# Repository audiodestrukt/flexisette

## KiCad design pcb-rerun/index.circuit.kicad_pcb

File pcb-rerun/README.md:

# pcb-rerun — flexisette re-driven unattended (2026-10-04)

A side-by-side re-run of the PCB next to the shipped board in [`../pcb`](../pcb). Same circuit and
same floorplan, routed with nobody touching KiCad, using the current
[circuit-skills](https://github.com/punkfab/circuit-skills) tooling.

## Result

| | Shipped (`../pcb`, June) | Re-run (this folder) |
|---|---|---|
| Open connections | 10 | **0** |
| Shorts | 0 | 0 |
| DRC errors (JLCPCB rules) | 5 (3 hole clearance, 1 edge clearance, 1 drill) | **0** |
| SMD pads not reached on their own layer | 4 | **0** |
| Vias | 26 | 47 |
| Track length | 1263 mm | 1000 mm |
| Ground carried as track instead of pour | 350 mm | 44 mm |
| Route time | hours of iteration, then a ~10-net tail left for hand-finishing | 6 s |

Checks on the re-run board:

- KiCad DRC at every severity: 0 errors, 0 unconnected, 5 silkscreen warnings.
- `dfm_check` (hole spacing, via drill and annular ring) passes.
- `check_floating` passes for all 106 SMD pads.
- The netlist is identical to the shipped board's: 22 nets, the same pads on each.

It has not been through JLCPCB's online DFM or a human review. Do both before ordering.

## What changed

**The route starts from the placed KiCad board, not from tscircuit's DSN export.** `scripts/route2.sh`
exports the placement, strips tscircuit's own routing, adds the bottom ground pour, applies JLCPCB
rules, and then runs every router on the KiCad board itself and scores them
(`scripts/route_eval.py`). Freerouting goes through KiCad's own Specctra export and import. The pour
goes out as a plane and the tape window, reel holes and screw holes go out as keepouts, so the router
sees the real board. This also closes roadmap gap #1 ("round-trip placement doesn't reach the routing
DSN"): there is no second copy of the placement to drift.

**Three placement changes**, each named by the tooling and made in the design source:

| Part | Change | Why |
|---|---|---|
| `SW_A`, `SW_B` | up 0.5 mm | A button pad was 0.455 mm from the head-notch edge. |
| `C1` (ESP32 3V3 decoupling, bottom side) | 2 mm inboard, under the module | Directly under the pin it sat against the board edge, and one bottom track boxed its ground pad off from the pour. |
| `C_BAT` | moved to the charger's BAT pin, placed by pin (`Decap`) | It was on the far side of the charger, 5 mm of crowded routing from the pin it decouples. Freerouting left that connection open. |

**Four tooling fixes** this board forced, all now in circuit-skills:

- **Ref-less footprints.** KiCad silently refuses to export a board that has a footprint with an empty reference. tscircuit exports bare holes and vias that way, which is why Freerouting-on-the-KiCad-board had never worked on a tscircuit design.
- **Keepout margin.** Cutout keepouts are grown by the copper-to-edge clearance. Otherwise a track ran 0.14 mm from the tape window.
- **Pour connection.** The pour connects SMD pads solidly, with thermal reliefs on through-hole pads only.
- **Capacity autorouter outline.** `route_srj` now gives the router the real outline polygon and the cutouts. It used to see only the bounding box.

The capacity autorouter's candidate also connects everything with no shorts, but leaves 14 clearance
violations (`results/candidate-srj.kicad_pcb`). Freerouting's is the one kept.

## Reproduce

```bash
cd pcb-rerun
npm install                 # or: ln -s ../pcb/node_modules node_modules
bash scripts/route2.sh      # ~30 s: export -> gates -> prep -> route with every backend -> apply the best -> DRC
```

Needs bun/tsci, KiCad 9 (`kicad-cli` and the system python `pcbnew` module), and Freerouting 2.2.4
(`freert224`). No running KiCad is required.

## results/

| file | what |
|---|---|
| `compare.jpg` | shipped vs re-run, with open connections and DRC errors marked |
| `route-eval-summary.md` | the scored table for both routers and the diagnosis |
| `candidate-srj.kicad_pcb` | the capacity autorouter's candidate |
| `placement-heat.svg` | congestion map of the placement before routing |

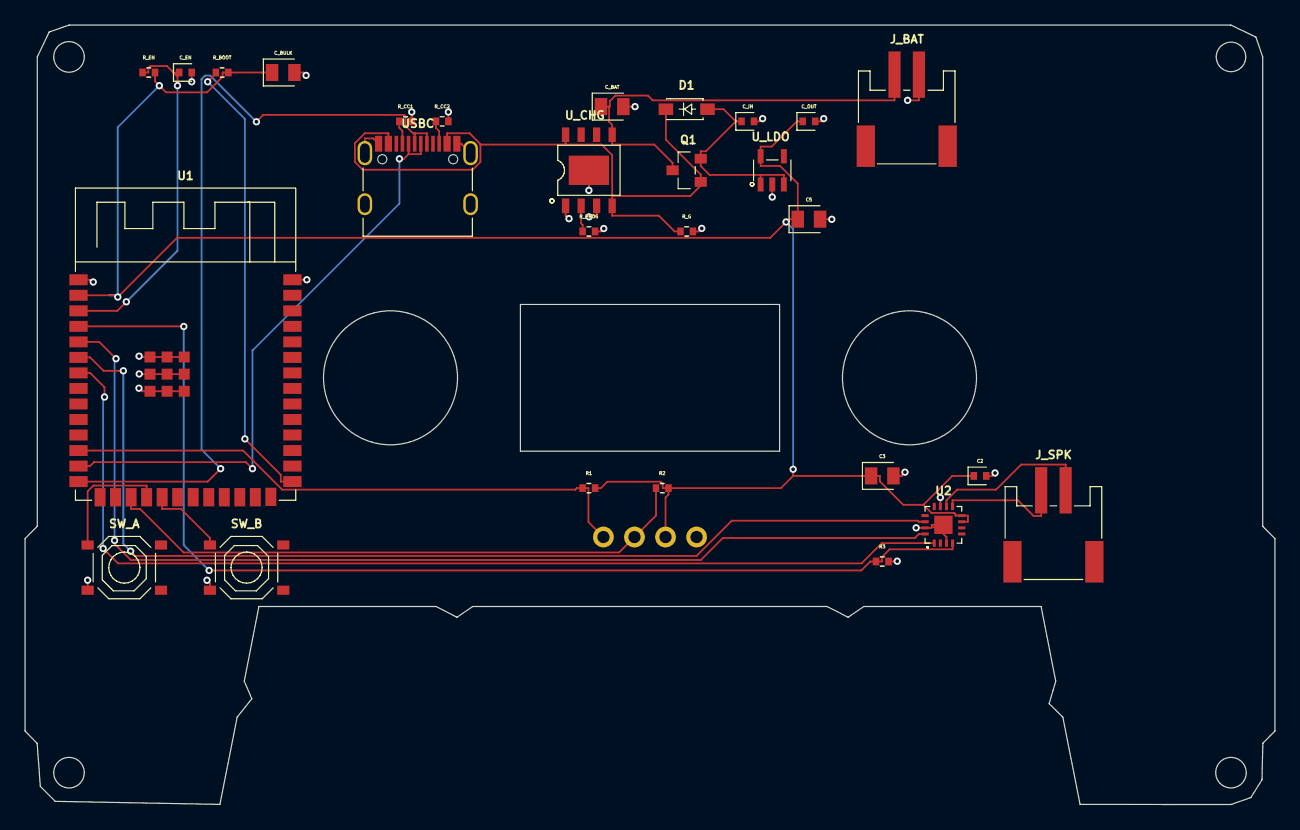
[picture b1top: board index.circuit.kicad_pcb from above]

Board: 2 copper layers, 102.2 x 63.8 mm, 30 parts (0 on the bottom side), 22 nets.

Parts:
C1, C2: 100nF; capacitor_0402
C3: 10uF; capacitor_0805
C5: 22uF; capacitor_0805
C_BAT: 10uF; capacitor_0805
C_BULK: 22uF; capacitor_0805
C_EN: 100nF; capacitor_0402
C_IN: 1uF; capacitor_0402
C_OUT: 1uF; capacitor_0402
D1: D; B5819W_SL
J_BAT: S2B_PH_SM4_TB_LF__SN_; S2B_PH_SM4_TB_LF_SN
J_SPK: S2B_PH_SM4_TB_LF__SN_; S2B_PH_SM4_TB_LF_SN
OLED: chip
Q1: AO3401A
R1, R2: 4.7kΩ; resistor_res0402
R3: 100kΩ; resistor_res0402
R_BOOT: 10kΩ; resistor_res0402
R_CC1, R_CC2: 5.1kΩ; resistor_res0402
R_EN: 10kΩ; resistor_res0402
R_G: 100kΩ; resistor_res0402
R_PROG: 2kΩ; resistor_res0402
SW_A: TS_1187A_B_A_B
SW_B: TS_1187A_B_A_B
U1: ESP32_S3_WROOM_1_N16R8
U2: MAX98357AETE_T
USBC: TYPE_C_31_M_12
U_CHG: TP4056_42_ESOP8
U_LDO: ME6211C33M5G_N

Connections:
BCK: U1.5, U2.16
DIN: U1.7, U2.1
GND: C1.2, C2.2, C3.2, C5.2, C_BAT.2, C_BULK.2, C_EN.2, C_IN.2, C_OUT.2, J_BAT.2, OLED.1, R3.2, R_CC1.2, R_CC2.2, R_G.2, R_PROG.2, SW_A.3, SW_B.3, U1.1, U1.40, U1.41, U1.42, U1.43, U1.44, U1.45, U1.46, U1.47, U1.48, U1.49, U2.3, U2.11, U2.15, U2.17, USBC.1, USBC.2, USBC.3, USBC.4, USBC.13, USBC.14, U_CHG.1, U_CHG.3, U_CHG.9, U_LDO.2
SCL: OLED.3, R2.1, U1.17
SD: R3.1, U1.4, U2.4
SDA: OLED.4, R1.1, U1.12
U1.EN to R_EN.pin1: C_EN.1, R_EN.1, U1.3
U1.IO0 to R_BOOT.pin1: R_BOOT.1, U1.27
U1.IO10 to SW_A.A: SW_A.1, U1.18
U1.IO11 to SW_B.A: SW_B.1, U1.19
U2.OUTN to J_SPK.pin2: J_SPK.2, U2.10
U2.OUTP to J_SPK.pin1: J_SPK.1, U2.9
USBC.A5 to R_CC1.pin1: R_CC1.1, USBC.6
USBC.B5 to R_CC2.pin1: R_CC2.1, USBC.12
USB_DM: U1.13, USBC.7, USBC.9
USB_DP: U1.14, USBC.8, USBC.10
U_CHG.PROG to R_PROG.pin1: R_PROG.1, U_CHG.2
V3V3: C1.1, C2.1, C3.1, C5.1, C_BULK.1, C_OUT.1, OLED.2, R1.2, R2.2, R_BOOT.2, R_EN.2, U1.2, U2.7, U2.8, U_LDO.5
VBAT: C_BAT.1, J_BAT.1, Q1.3, U_CHG.5
VBUS: D1.1, Q1.1, R_G.1, USBC.15, USBC.16, U_CHG.4, U_CHG.8
VSYS: C_IN.1, D1.2, Q1.2, U_LDO.1, U_LDO.3
WS: U1.6, U2.14
